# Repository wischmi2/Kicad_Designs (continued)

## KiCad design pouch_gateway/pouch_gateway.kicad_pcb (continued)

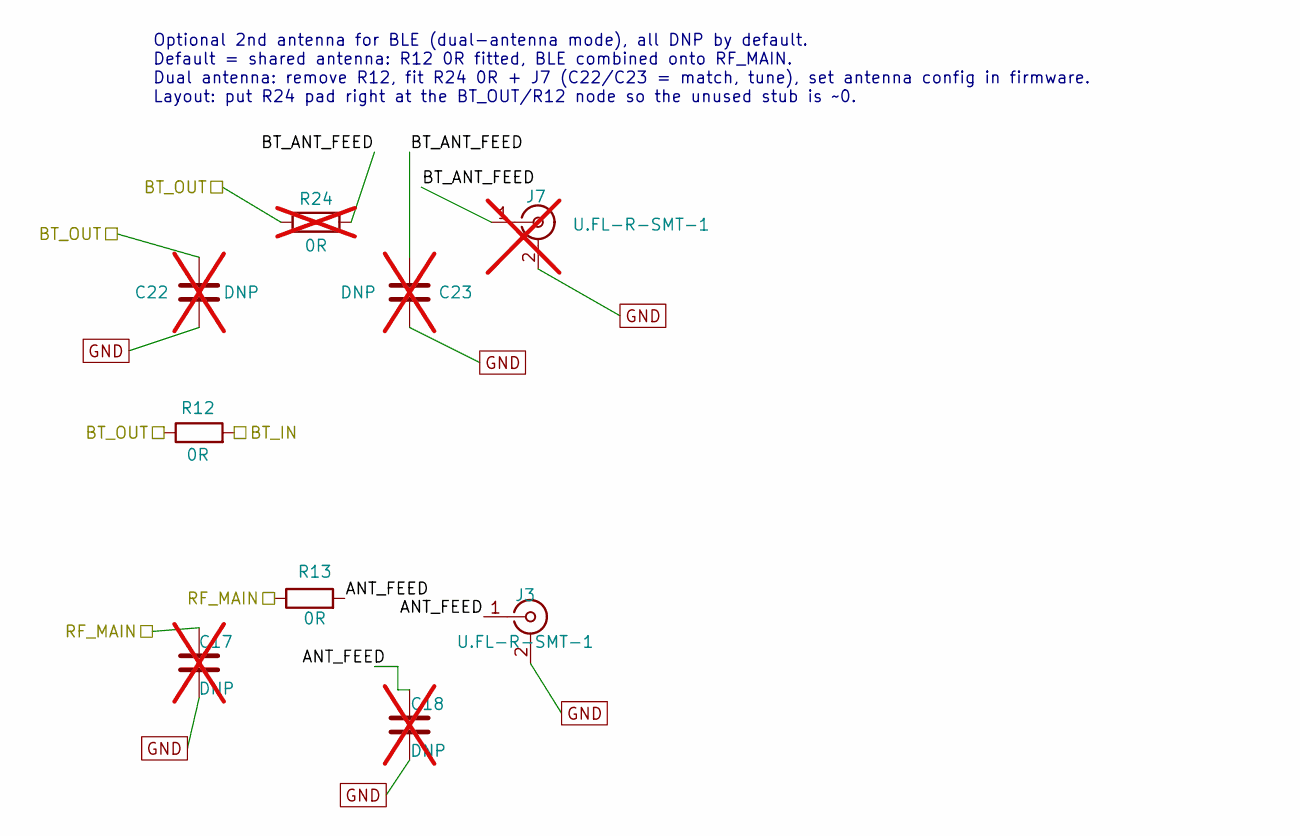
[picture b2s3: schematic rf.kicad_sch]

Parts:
C17, C18: DNP; C_0402_1005Metric; not fitted
C22, C23: DNP; C_0402_1005Metric; LCSC C1525; not fitted
J3: U.FL-R-SMT-1; U.FL_Hirose_U.FL-R-SMT-1_Vertical; LCSC C128668
J7: U.FL-R-SMT-1; U.FL_Hirose_U.FL-R-SMT-1_Vertical; LCSC C128668; not fitted
R12, R13: 0R; R_0402_1005Metric; LCSC C17168
R24: 0R; R_0402_1005Metric; LCSC C17168; not fitted

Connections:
/MCU/BT_IN: R12.2; also elsewhere on the board
/MCU/BT_OUT: C22.1, R12.1, R24.1; also elsewhere on the board
/MCU/RF_MAIN: C17.1, R13.1; also elsewhere on the board
/RF/ANT_FEED: C18.1, J3.1 (In), R13.2
/RF/BT_ANT_FEED: C23.1, J7.1 (In), R24.2
GND: C17.2, C18.2, C22.2, C23.2, J3.2 (Ext), J7.2 (Ext); also elsewhere on the board

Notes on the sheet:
Optional 2nd antenna for BLE (dual-antenna mode), all DNP by default. Default = shared antenna: R12 0R fitted, BLE combined onto RF_MAIN. Dual antenna: remove R12, fit R24 0R + J7 (C22/C23 = match, tune), set antenna config in firmware. Layout: put R24 pad right at the BT_OUT/R12 node so the unused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

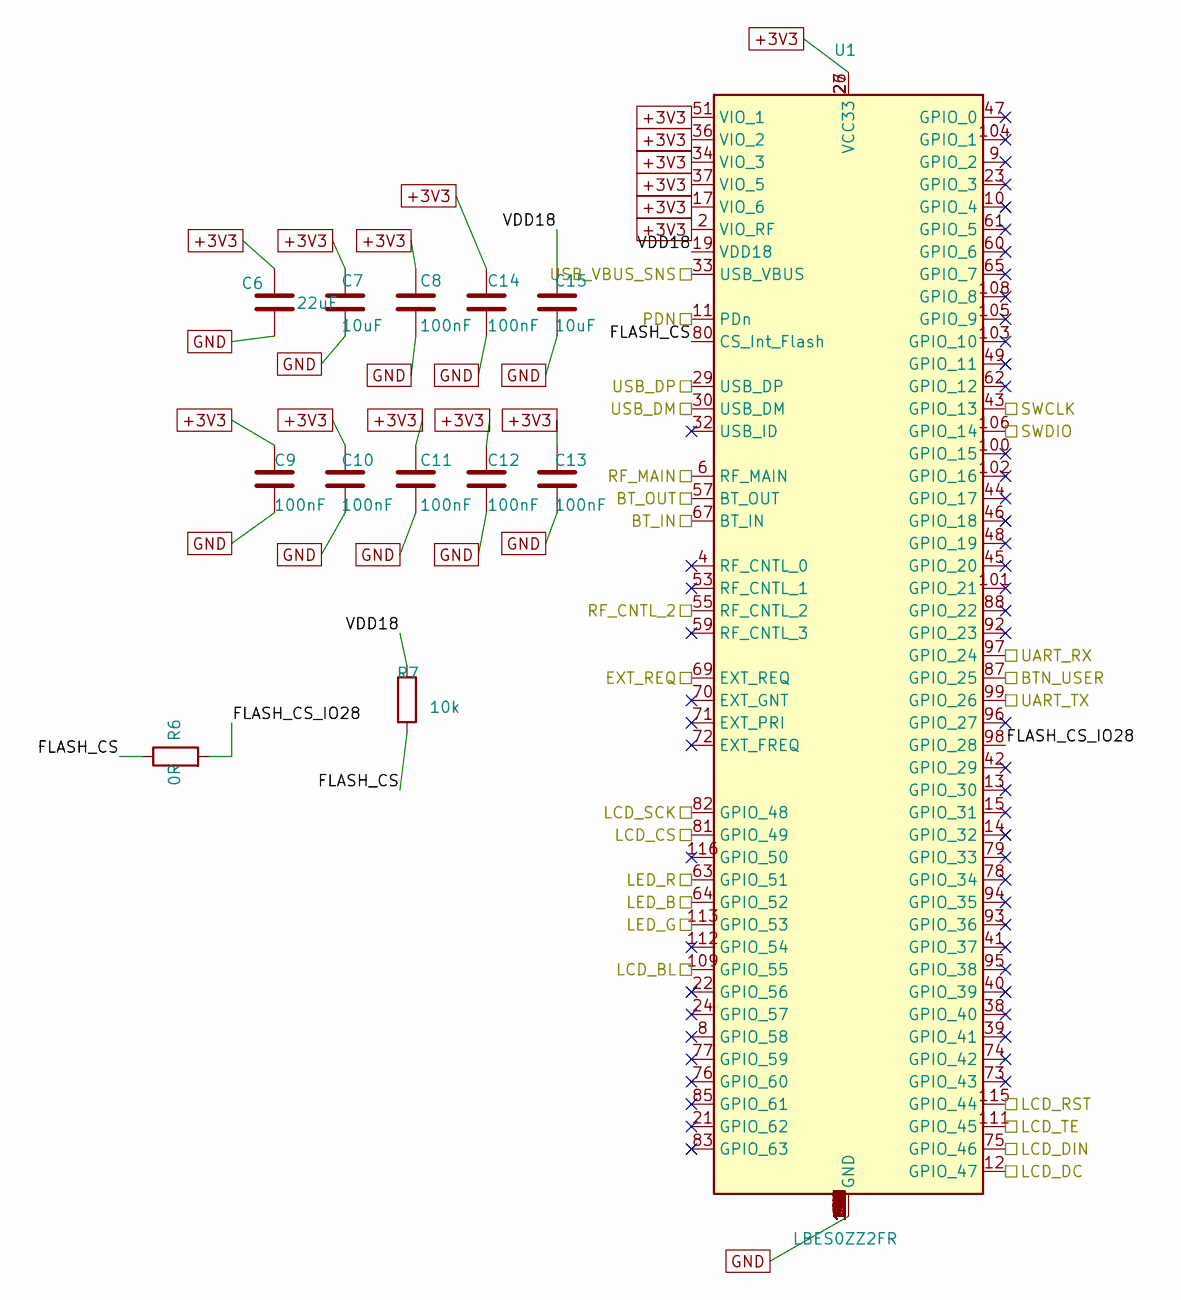
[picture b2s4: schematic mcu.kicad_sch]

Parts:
C6: 22uF; C_0805_2012Metric; LCSC C45783
C7, C15: 10uF; C_0603_1608Metric; LCSC C19702
C8, C9, C10, C11, C12, C13, C14: 100nF; C_0402_1005Metric; LCSC C1525
R6: 0R; R_0402_1005Metric; LCSC C17168
R7: 10k; R_0402_1005Metric; LCSC C25744
U1: LBES0ZZ2FR; Murata_LBES0ZZ2FR; MPN LBES0ZZ2FR-580

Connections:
+3V3: C6.1, C7.1, C8.1, C9.1, C10.1, C11.1, C12.1, C13.1, C14.1, U1.2 (VIO_RF), U1.17 (VIO_6), U1.26 (VCC33), U1.27 (VCC33), U1.34 (VIO_3), U1.36 (VIO_2), U1.37 (VIO_5), U1.51 (VIO_1); also elsewhere on the board
/MCU/BTN_USER: U1.87 (GPIO_25); also elsewhere on the board
/MCU/BT_IN: U1.67 (BT_IN); also elsewhere on the board
/MCU/BT_OUT: U1.57 (BT_OUT); also elsewhere on the board
/MCU/EXT_REQ: U1.69 (EXT_REQ); also elsewhere on the board
/MCU/FLASH_CS: R6.1, R7.2, U1.80 (CS_Int_Flash)
/MCU/FLASH_CS_IO28: R6.2, U1.98 (GPIO_28)
/MCU/LCD_BL: U1.109 (GPIO_55); also elsewhere on the board
/MCU/LCD_CS: U1.81 (GPIO_49); also elsewhere on the board
/MCU/LCD_DC: U1.12 (GPIO_47); also elsewhere on the board
/MCU/LCD_DIN: U1.75 (GPIO_46); also elsewhere on the board
/MCU/LCD_RST: U1.115 (GPIO_44); also elsewhere on the board
/MCU/LCD_SCK: U1.82 (GPIO_48); also elsewhere on the board
/MCU/LCD_TE: U1.111 (GPIO_45); also elsewhere on the board
/MCU/LED_B: U1.64 (GPIO_52); also elsewhere on the board
/MCU/LED_G: U1.113 (GPIO_53); also elsewhere on the board
/MCU/LED_R: U1.63 (GPIO_51); also elsewhere on the board
/MCU/PDN: U1.11 (PDn); also elsewhere on the board
/MCU/RF_CNTL_2: U1.55 (RF_CNTL_2); also elsewhere on the board
/MCU/RF_MAIN: U1.6 (RF_MAIN); also elsewhere on the board
/MCU/SWCLK: U1.43 (GPIO_13); also elsewhere on the board
/MCU/SWDIO: U1.106 (GPIO_14); also elsewhere on the board
/MCU/UART_RX: U1.97 (GPIO_24); also elsewhere on the board
/MCU/UART_TX: U1.99 (GPIO_26); also elsewhere on the board
/MCU/USB_DM: U1.30 (USB_DM); also elsewhere on the board
/MCU/USB_DP: U1.29 (USB_DP); also elsewhere on the board
/MCU/USB_VBUS_SNS: U1.33 (USB_VBUS); also elsewhere on the board
/MCU/VDD18: C15.1, R7.1, U1.19 (VDD18)
GND: C6.2, C7.2, C8.2, C9.2, C10.2, C11.2, C12.2, C13.2, C14.2, C15.2, U1.1 (GND), U1.3 (GND), U1.5 (GND), U1.7 (GND), U1.16 (GND), U1.18 (GND), U1.20 (GND), U1.25 (GND), U1.28 (GND), U1.31 (GND), U1.35 (GND), U1.50 (GND), U1.52 (GND), U1.54 (GND), U1.56 (GND), U1.58 (GND), U1.66 (GND), U1.68 (GND), U1.84 (GND), U1.86 (GND), U1.89 (GND), U1.90 (GND), U1.91 (GND), U1.107 (GND), U1.110 (GND), U1.114 (GND), U1.117 (GND), U1.118 (GND), U1.119 (GND), U1.120 (GND), U1.121 (GND), U1.122 (GND), U1.123 (GND), U1.124 (GND), U1.125 (GND), U1.126 (GND), U1.127 (GND), U1.128 (GND), U1.129 (GND), U1.130 (GND), U1.131 (GND), U1.132 (GND), U1.133 (GND), U1.134 (GND), U1.135 (GND), U1.136 (GND), U1.137 (GND), U1.138 (GND), U1.139 (GND), U1.140 (GND); also elsewhere on the board

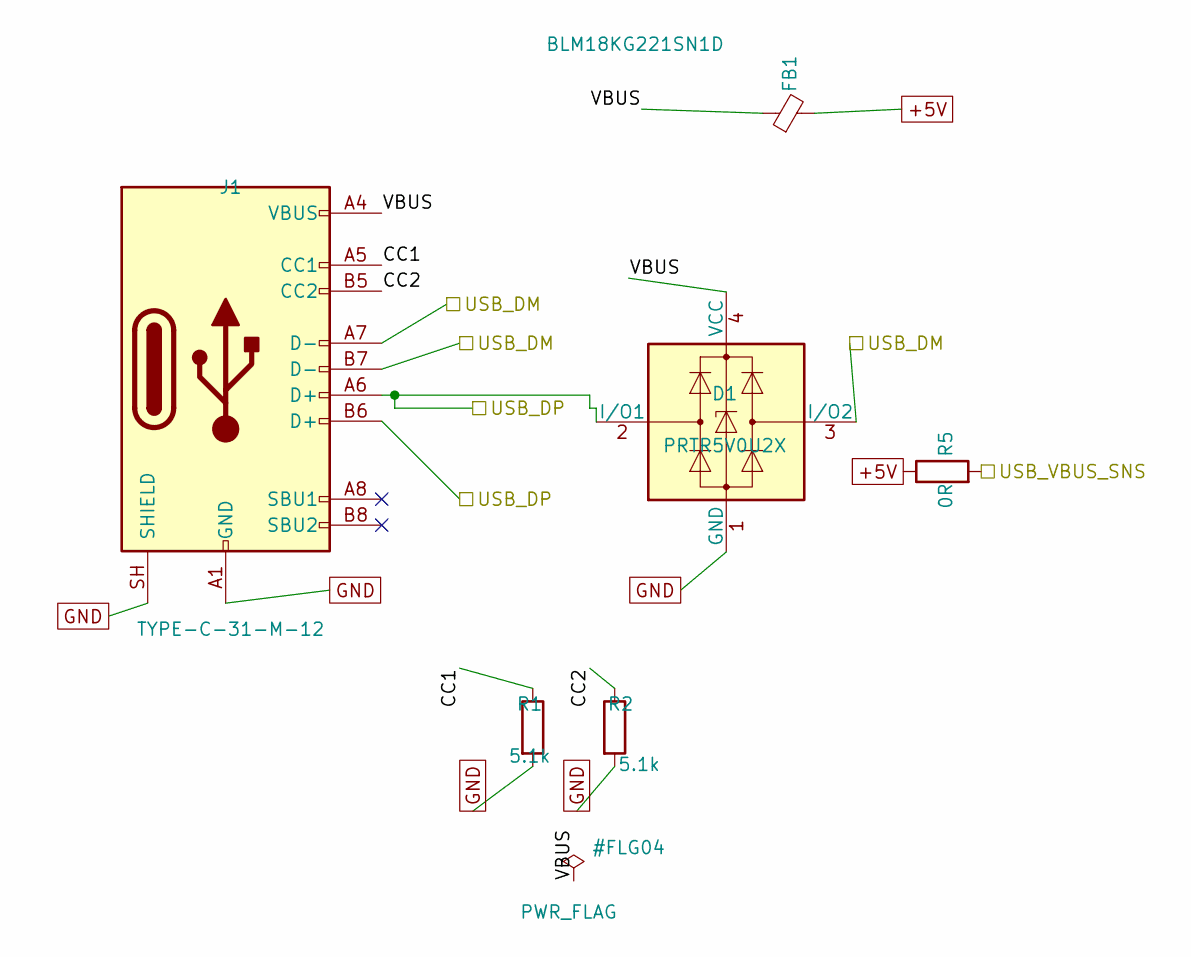
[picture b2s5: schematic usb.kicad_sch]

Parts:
D1: PRTR5V0U2X; SOT-143; LCSC C21713980
FB1: BLM18KG221SN1D; L_0603_1608Metric; LCSC C88980
J1: TYPE-C-31-M-12; USB_C_Receptacle_HRO_TYPE-C-31-M-12; LCSC C165948
R1, R2: 5.1k; R_0402_1005Metric; LCSC C25905
R5: 0R; R_0402_1005Metric; LCSC C17168

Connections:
+5V: FB1.2, R5.1; also elsewhere on the board
/MCU/USB_DM: D1.3 (I/O2), J1.A7 (D-), J1.B7 (D-); also elsewhere on the board
/MCU/USB_DP: D1.2 (I/O1), J1.A6 (D+), J1.B6 (D+); also elsewhere on the board
/MCU/USB_VBUS_SNS: R5.2; also elsewhere on the board
/USB/CC1: J1.A5 (CC1), R1.1
/USB/CC2: J1.B5 (CC2), R2.1
/USB/VBUS: D1.4 (VCC), FB1.1, J1.A4 (VBUS), J1.A9 (VBUS), J1.B4 (VBUS), J1.B9 (VBUS)
GND: D1.1 (GND), J1.A1 (GND), J1.A12 (GND), J1.B1 (GND), J1.B12 (GND), J1.SH (SHIELD), R1.2, R2.2; also elsewhere on the board

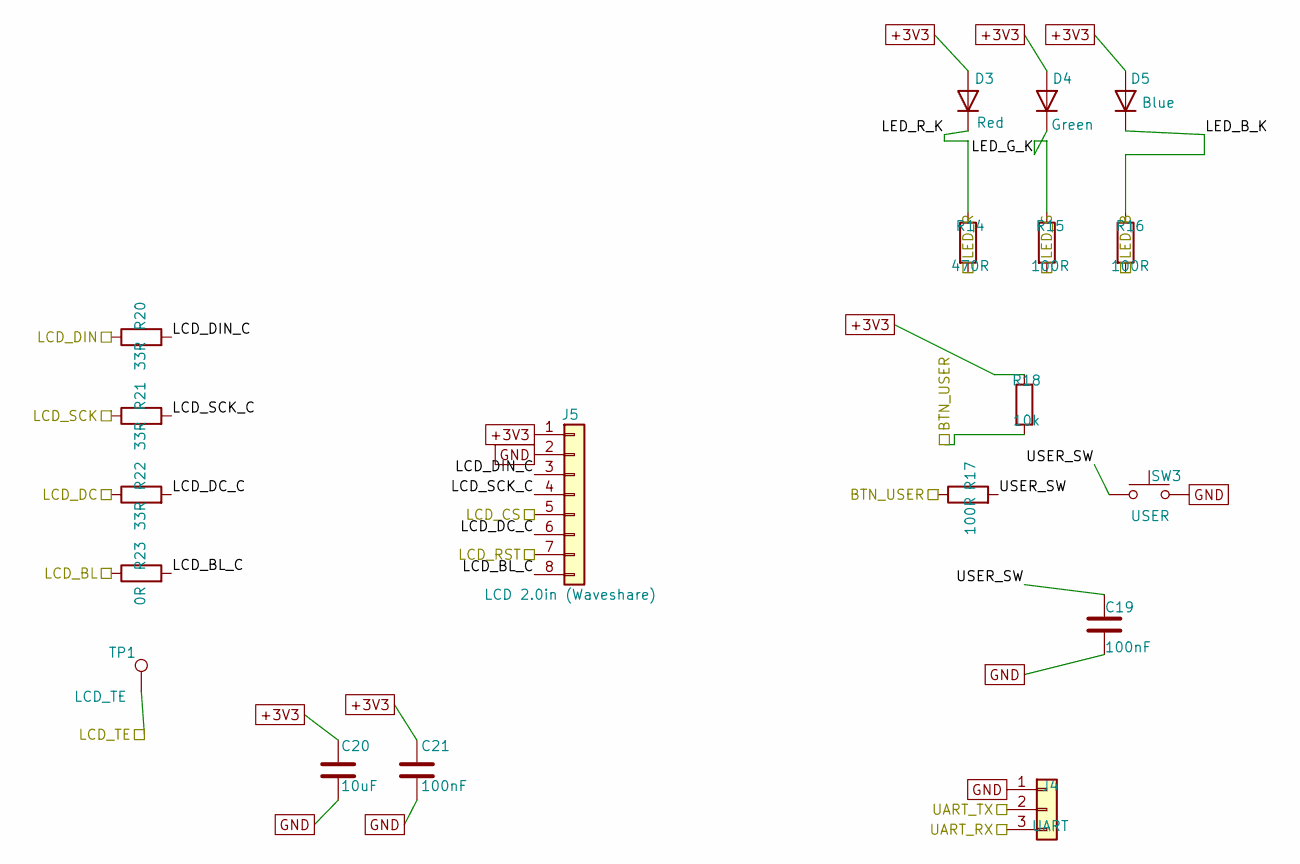
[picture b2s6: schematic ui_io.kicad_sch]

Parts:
C19, C21: 100nF; C_0402_1005Metric; LCSC C1525
C20: 10uF; C_0603_1608Metric; LCSC C19702
D3: Red; LED_0603_1608Metric; LCSC C2286
D4: Green; LED_0805_2012Metric; LCSC C2297
D5: Blue; LED_0603_1608Metric; LCSC C125096
J4: UART; PinHeader_1x03_P2.54mm_Vertical; MPN PZ254V-11-03P; LCSC C2937625
J5: LCD 2.0in (Waveshare); JST_PH_S8B-PH-K_1x08_P2.00mm_Horizontal; MPN S8B-PH-K-S(LF)(SN); LCSC C157915
R14: 470R; R_0402_1005Metric; LCSC C25117
R15, R16, R17: 100R; R_0402_1005Metric; LCSC C25076
R18: 10k; R_0402_1005Metric; LCSC C25744
R20, R21, R22: 33R; R_0402_1005Metric; LCSC C25105
R23: 0R; R_0402_1005Metric; LCSC C17168
SW3: USER; SW_Push_1P1T_NO_CK_KMR2; LCSC C72443
TP1: LCD_TE; TestPoint_Pad_D1.0mm

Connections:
+3V3: C20.1, C21.1, D3.2 (A), D4.2 (A), D5.2 (A), J5.1, R18.1; also elsewhere on the board
/MCU/BTN_USER: R17.1, R18.2; also elsewhere on the board
/MCU/LCD_BL: R23.1; also elsewhere on the board
/MCU/LCD_CS: J5.5; also elsewhere on the board
/MCU/LCD_DC: R22.1; also elsewhere on the board
/MCU/LCD_DIN: R20.1; also elsewhere on the board
/MCU/LCD_RST: J5.7; also elsewhere on the board
/MCU/LCD_SCK: R21.1; also elsewhere on the board
/MCU/LCD_TE: TP1.1 (1_1); also elsewhere on the board
/MCU/LED_B: R16.2; also elsewhere on the board
/MCU/LED_G: R15.2; also elsewhere on the board
/MCU/LED_R: R14.2; also elsewhere on the board
/MCU/UART_RX: J4.3; also elsewhere on the board
/MCU/UART_TX: J4.2; also elsewhere on the board
/UI_IO/LCD_BL_C: J5.8, R23.2
/UI_IO/LCD_DC_C: J5.6, R22.2
/UI_IO/LCD_DIN_C: J5.3, R20.2
/UI_IO/LCD_SCK_C: J5.4, R21.2
/UI_IO/LED_B_K: D5.1 (K), R16.1
/UI_IO/LED_G_K: D4.1 (K), R15.1
/UI_IO/LED_R_K: D3.1 (K), R14.1
/UI_IO/USER_SW: C19.1, R17.2, SW3.1; also elsewhere on the board
GND: C19.2, C20.2, C21.2, J4.1, J5.2, SW3.2; also elsewhere on the board

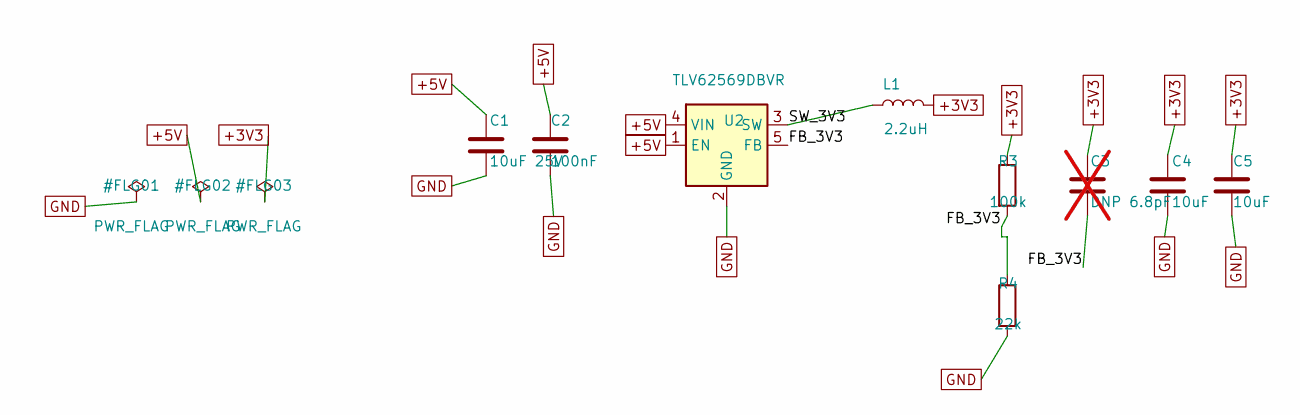
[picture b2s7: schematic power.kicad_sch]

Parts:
C1: 10uF 25V; C_0603_1608Metric; LCSC C96446
C2: 100nF; C_0402_1005Metric; LCSC C1525
C3: DNP 6.8pF; C_0402_1005Metric; not fitted
C4, C5: 10uF; C_0603_1608Metric; LCSC C19702
L1: 2.2uH; L_Sunlord_SWPA4020S; MPN SWPA4020S2R2MT; LCSC C83423
R3: 100k; R_0402_1005Metric; LCSC C25741
R4: 22k; R_0402_1005Metric; LCSC C25768
U2: TLV62569DBVR; SOT-23-5; LCSC C141836

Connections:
+3V3: C3.1, C4.1, C5.1, L1.2, R3.1; also elsewhere on the board
+5V: C1.1, C2.1, U2.1 (EN), U2.4 (VIN); also elsewhere on the board
/Power/FB_3V3: C3.2, R3.2, R4.1, U2.5 (FB)
/Power/SW_3V3: L1.1, U2.3 (SW)
GND: C1.2, C2.2, C4.2, C5.2, R4.2, U2.2 (GND); also elsewhere on the board

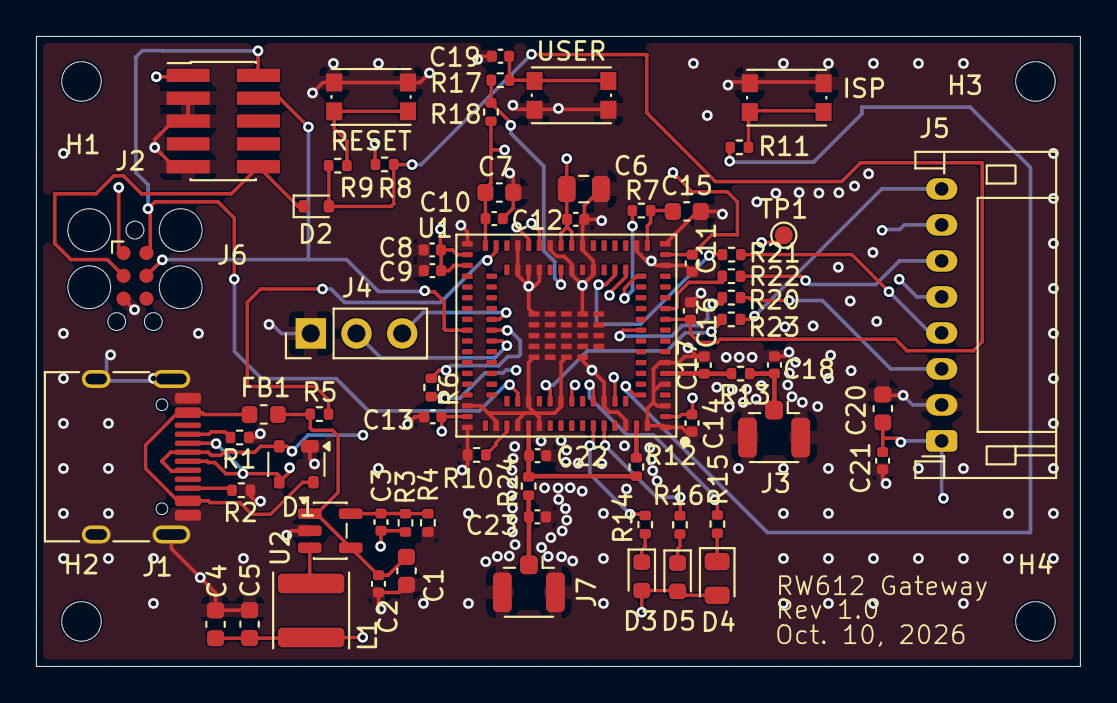
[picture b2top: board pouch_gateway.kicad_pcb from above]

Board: 4 copper layers, 58.0 x 35.0 mm, 70 parts (0 on the bottom side), 48 nets.

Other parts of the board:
ISP: ISP; SW_Push_1P1T_NO_CK_KMR2
RESET: RESET; SW_Push_1P1T_NO_CK_KMR2
USER: USER; SW_Push_1P1T_NO_CK_KMR2

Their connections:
/Reset_Debug_Boot/ISP_SW: ISP.1; also elsewhere on the board
/Reset_Debug_Boot/RST_SW: RESET.1; also elsewhere on the board
/UI_IO/USER_SW: USER.1; also elsewhere on the board
GND: ISP.2, RESET.2, USER.2; also elsewhere on the board

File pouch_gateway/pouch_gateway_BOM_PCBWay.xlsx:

|  |  | pouch_gateway — PCB Assembly BOM
Item # | *Designator | *Qty | Manufacturer | *Mfg Part # | Description / Value | *Package/Footprint | Type | Your Instructions / Notes
1 | C2,C8,C9,C10,C11,C12,C13,C14,C16,C19,C21 | 11 | Samsung Electro-Mechanics | CL05B104KO5NNNC | CAP CER 100nF 16V X7R ±10% 0402 | 0402 | SMD | LCSC: C1525
2 | C1 | 1 | Samsung Electro-Mechanics | CL10A106MA8NRNC | CAP CER 10uF 25V X5R ±20% 0603 | 0603 | SMD | LCSC: C96446 (25V rating required)
3 | C4,C5,C7,C15,C20 | 5 | Samsung Electro-Mechanics | CL10A106KP8NNNC | CAP CER 10uF 10V X5R ±10% 0603 | 0603 | SMD | LCSC: C19702
4 | C6 | 1 | Samsung Electro-Mechanics | CL21A226MAQNNNE | CAP CER 22uF 25V X5R ±20% 0805 | 0805 | SMD | LCSC: C45783
5 | R5,R6,R12,R13,R23 | 5 | UNI-ROYAL | 0402WGF0000TCE | RES 0 OHM JUMPER 1/16W 0402 | 0402 | SMD | LCSC: C17168
6 | R1,R2,R10,R11 | 4 | UNI-ROYAL | 0402WGF5101TCE | RES 5.1K OHM 1% 1/16W 0402 | 0402 | SMD | LCSC: C25905
7 | R7,R8,R18 | 3 | UNI-ROYAL | 0402WGF1002TCE | RES 10K OHM 1% 1/16W 0402 | 0402 | SMD | LCSC: C25744
8 | R3 | 1 | UNI-ROYAL | 0402WGF1003TCE | RES 100K OHM 1% 1/16W 0402 | 0402 | SMD | LCSC: C25741
9 | R4 | 1 | UNI-ROYAL | 0402WGF2202TCE | RES 22K OHM 1% 1/16W 0402 | 0402 | SMD | LCSC: C25768
10 | R9,R15,R16,R17 | 4 | UNI-ROYAL | 0402WGF1000TCE | RES 100 OHM 1% 1/16W 0402 | 0402 | SMD | LCSC: C25076
11 | R14 | 1 | UNI-ROYAL | 0402WGF4700TCE | RES 470 OHM 1% 1/16W 0402 | 0402 | SMD | LCSC: C25117
12 | R20,R21,R22 | 3 | UNI-ROYAL | 0402WGF330JTCE | RES 33 OHM 1% 1/16W 0402 | 0402 | SMD | LCSC: C25105
13 | FB1 | 1 | Murata | BLM18KG221SN1D | FERRITE BEAD 220 OHM @100MHz 2.2A 0603 | 0603 | SMD | LCSC: C88980
14 | L1 | 1 | Sunlord | SWPA4020S2R2MT | INDUCTOR PWR 2.2uH ±20% 4x4mm SMD | SMD 4.0x4.0mm | SMD | LCSC: C83423
15 | D1 | 1 | GOODWORK | PRTR5V0U2X | TVS ESD 2-CH USB PROTECTION SOT-143 | SOT-143 | SMD | LCSC: C21713980; Nexperia PRTR5V0U2X acceptable alternate. Polarity per silkscr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
16 | D2 | 1 | onsemi | RB521S30T1G | DIODE SCHOTTKY 30V 200mA SOD-523 | SOD-523 | SMD | LCSC: C145179; polarity per silkscreen
17 | D3 | 1 | Hubei KENTO | KT-0603R | LED RED 0603 | 0603 | SMD | LCSC: C2286; polarity per silkscreen
18 | D4 | 1 | Hubei KENTO | KT-0805G | LED GREEN 0805 | 0805 | SMD | LCSC: C2297; polarity per silkscreen
19 | D5 | 1 | Lite-On | LTST-C190TBKT | LED BLUE 0603 | 0603 | SMD | LCSC: C125096; polarity per silkscreen
20 | U1 | 1 | Murata | LBES0ZZ2FR-580 | MODULE WI-FI/BLE (Murata Type 2FR) | Murata LBES0ZZ2FR module, SMD | SMD | No LCSC part #; please quote sourcing. Pin 1 per silkscreen
21 | U2 | 1 | Texas Instruments | TLV62569DBVR | IC REG BUCK ADJ 2A SOT-23-5 | SOT-23-5 | SMD | LCSC: C141836; pin 1 per silkscreen
22 | J1 | 1 | Korean Hroparts Elec (HRO) | TYPE-C-31-M-12 | CONN USB TYPE-C RCPT 16P SMD R/A | SMD | SMD | LCSC: C165948
23 | J2 | 1 | Samtec | FTSH-105-01-L-DV-K-TR | CONN HDR 2x5 1.27mm SMD VERT (SWD) | 2x5 P1.27mm SMD | SMD | LCSC: C448647; pin 1 per silkscreen
24 | J3 | 1 | Hirose | U.FL-R-SMT-1(60) | CONN U.FL RF COAX RCPT SMD | SMD | SMD | LCSC: C128668
25 | ISP,RESET,USER | 3 | C&K | KMR221GLFS | SWITCH TACTILE SPST-NO 50mA 32V SMD | SMD 4.6x2.8mm | SMD | LCSC: C72443
26 | J4 | 1 | XFCN | PZ254V-11-03P | CONN HDR 1x3 2.54mm VERT THT | 1x3 P2.54mm THT | thru-hole | LCSC: C2937625
27 | J5 | 1 | JST | S8B-PH-K-S(LF)(SN) | CONN HDR PH 8POS 2.0mm R/A THT | 1x8 P2.00mm R/A THT | thru-hole | LCSC: C157915
28 | C3 | 1 |  |  | CAP CER 6.8pF 0402 (not fitted) | 0402 | DNS | Do not populate
29 | C17,C18 | 2 |  |  | CAP CER 0402 (not fitted) | 0402 | DNS | Do not populate
30 | C22,C23 | 2 |  |  | CAP CER 100nF 0402 (not fitted) | 0402 | DNS | Do not populate
31 | R24 | 1 |  |  | RES 0 OHM 0402 (not fitted) | 0402 | DNS | Do not populate
32 | J7 | 1 |  |  | CONN U.FL RF COAX RCPT SMD (not fitted) | SMD | DNS | Do not populate
Need a quick and accurante quote? Need an efficient production? Please read SMT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
Click for Instructions on How to Create a BOM

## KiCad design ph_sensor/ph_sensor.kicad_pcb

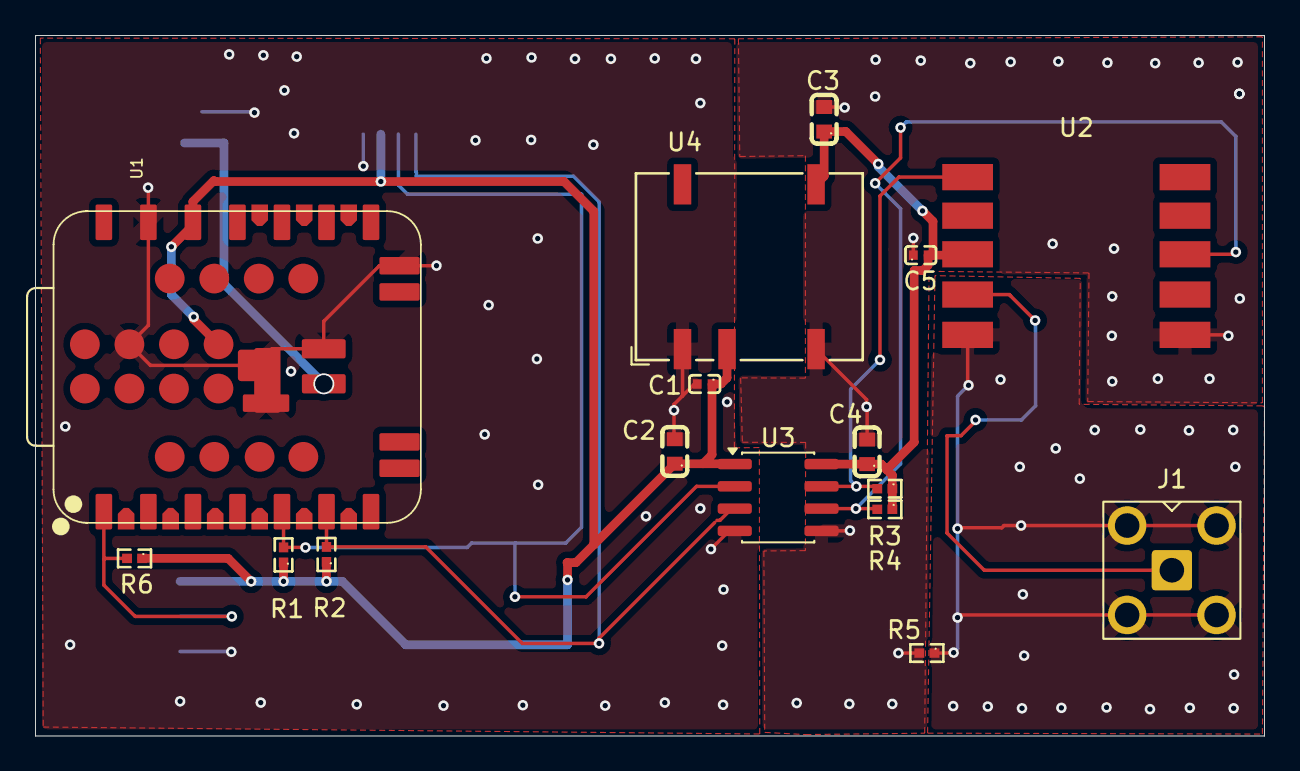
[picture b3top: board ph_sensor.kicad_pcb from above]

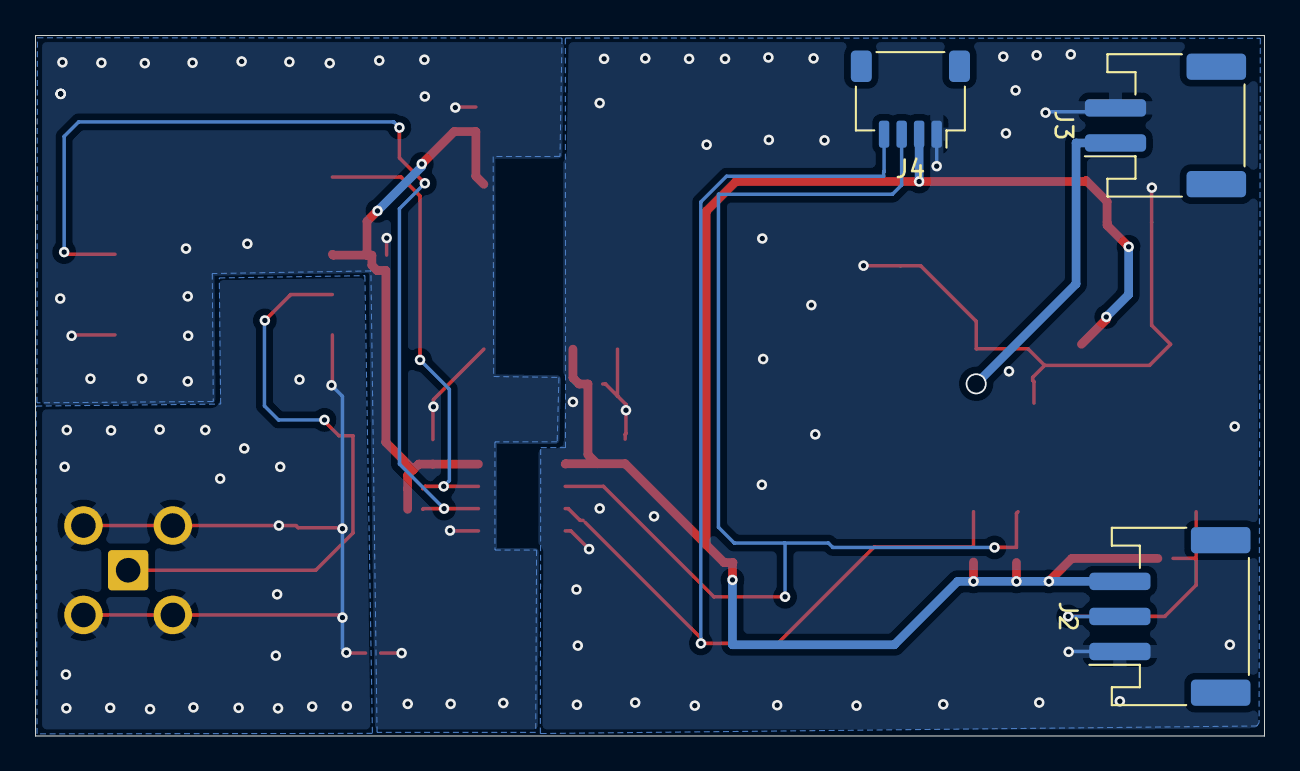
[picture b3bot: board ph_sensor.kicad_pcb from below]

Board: 2 copper layers, 70.1 x 40.0 mm, 19 parts (3 on the bottom side), 12 nets.

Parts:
C1, C5: 1uF; C0402
C2, C4: 100nF; C0603
C3: 2.2uF; C0603
J1: Conn_Coaxial_Small; SMA_BAT_Wireless_BWSMA-KWE-Z001
J2: Conn_01x03; JST_PH_S3B-PH-SM4-TB_1x03-1MP_P2.00mm_Horizontal
J3: Conn_01x02; JST_PH_S2B-PH-SM4-TB_1x02-1MP_P2.00mm_Horizontal
J4: Conn_01x04; JST_SH_SM04B-SRSS-TB_1x04-1MP_P1.00mm_Horizontal
R1, R2, R3, R4, R6: 4.7k; R0402
R5: 0; R0402
U1: XIAO-nRF54LM20A-SMD
U2: Atlas_pH_OEM
U3: ADuM1250; SOIC-8_3.9x4.9mm_P1.27mm
U4: NXE1S0303MC; Converter_DCDC_Murata_NXExSxxxxMC_SMD

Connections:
+3.3V: C1.1, C2.1, J2.3, J4.2, R1.1, R2.1, R6.1, U1.12 (3V3_OUT), U1.39 (3V3_OUT), U3.1 (VDD1), U4.3 (+Vin)
+3v3V_ISO: C3.1, C4.1, C5.2, R3.1, R4.1, U2.3 (VCC), U3.8 (VDD2), U4.8 (+Vout)
AGND_ISO: J1.2 (Ext), R5.1, U2.5 (PRB_GND)
GND: C1.2, C2.2, J2.1, J3.2, J4.1, U1.13 (GND), U1.35 (GND), U1.41 (GND), U1.42 (GND), U1.46 (GND), U3.4 (GND1), U4.1 (-Vin)
GND_ISO: C3.2, C4.2, C5.1, R5.2, U2.6 (GND), U3.5 (GND2), U4.7 (-Vout)
unnamed: J1.1 (In), U2.4 (PRB)
SCL_H: J4.4, R2.2, U1.6 (D5), U3.3 (SCL1)
SCL_ISO: R4.2, U2.8 (SCL), U3.6 (SCL2)
SDA_H: J4.3, R1.2, U1.5 (D4), U3.2 (SDA1)
SDA_ISO: R3.2, U2.1 (SDA), U3.7 (SDA2)
TEMP_DQ: J2.2, R6.2, U1.1 (D0)
VBAT: J3.1, U1.40 (VBAT)

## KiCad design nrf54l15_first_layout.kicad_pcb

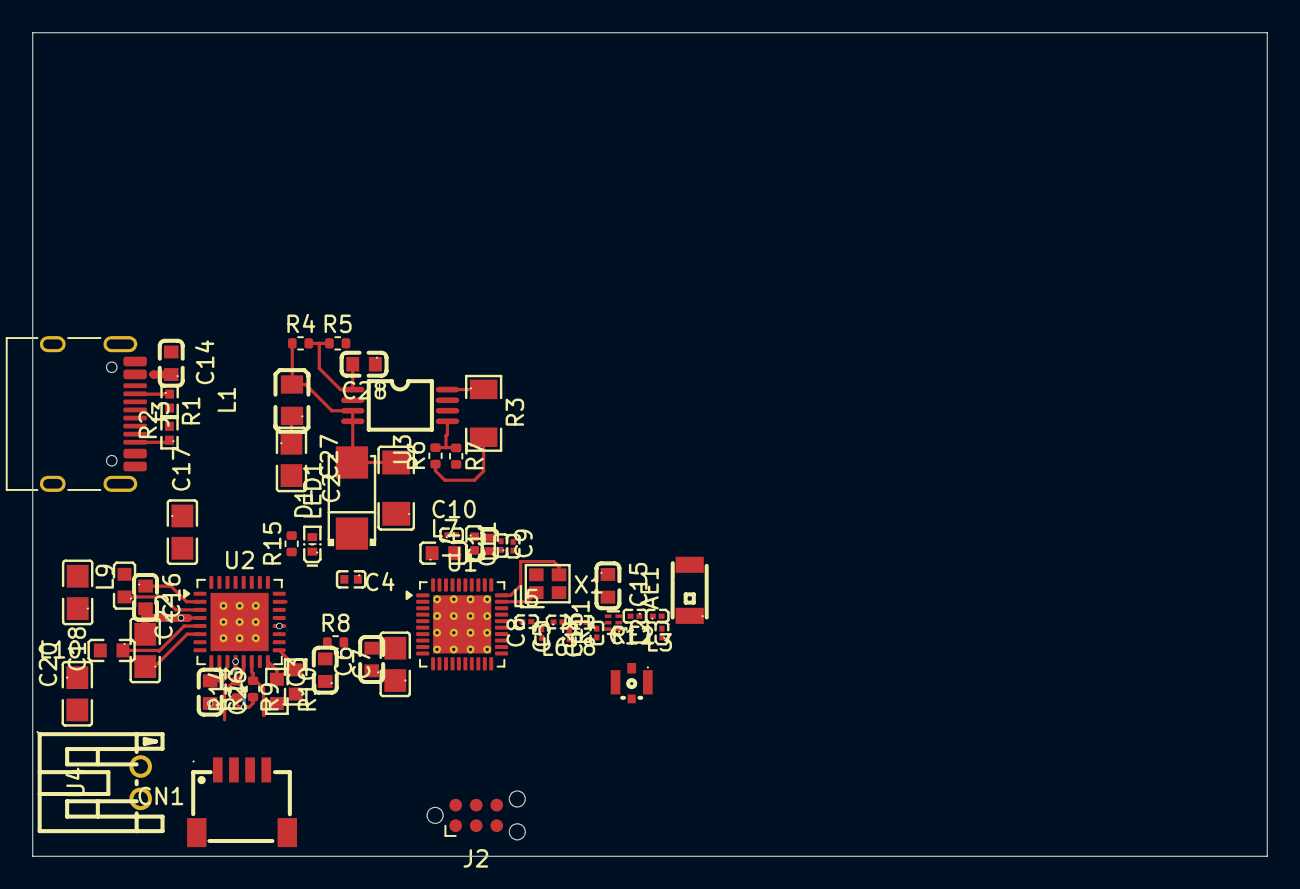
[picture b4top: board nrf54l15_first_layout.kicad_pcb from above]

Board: 4 copper layers, 76.4 x 51.0 mm, 59 parts (0 on the bottom side), 42 nets.

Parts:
AE1: 2450AT18A100E; ANT-SMD_L3.2-W1.6
C1, C10: 2.2uF; C0201
C2: 47uF; C1206
C3: 2.2uF; C0603
C4: 1uF; C0402
C5: 2.0pF; C0201
C6, C14, C15, C26, C28: 100nF; C0603
C7, C17, C18, C20, C22, C27: 10uF; C0805
C8: 1.5pF; C0201
C9: 10nF; C0402
C11: 2.2pF; C0201
C12: 1.0pF; C0201
C13: 0.3pF; C0201
C16: 10uF; C0603
CN1: SM04B-SRSS-TB; CONN-SMD_4P-P1.00_SM04B-SRSS-TB-LF-SN
D1: SS14_C83852; SMA_L4.3-W2.6-LS5.2-RD
J2: TC2030; Tag-Connect_TC2030-IDC-NL_2x03_P1.27mm_Vertical
J3: USB_C_Receptacle_PowerOnly_6P; USB_C_Receptacle_HRO_TYPE-C-31-M-12
L1: SDFL2012S100KTF; L0805
L2, L5: 2.7nH; L0201
L3: 3.9nH; L0201
L4: CBG100505U121T; L0402
L6, L8: 3.5nH; L0201
L7: 4.7uH; L0603
L9, L10: 2.2uH; L0603
LED1: SML-P12MTT86R; LED-SMD_L1.0-W0.6-RD_SML-P12YTT86RR
R1, R2: 5.1k; R0402
R3: 100k; R1206
R4: 3.3M; R_0402_1005Metric
R5, R7: 1M; R_0402_1005Metric
R6: 3.9M; R_0402_1005Metric
R8: 10k; R_0402_1005Metric
R9: 47k; R0603
R10: 150k; R0603
R11: FM8625H; DFN-6_L1.1-W0.7-P0.40-BL
R13, R14: 4.7k; R_0402_1005Metric
R15: 560; R_0402_1005Metric
RF1: ECT818000500; ANT-SMD_ECT818000500
U1: nRF54L15-QDXX; QFN-40-1EP_5x5mm_P0.4mm_EP3.6x3.6mm_ThermalVias
U2: nPM1300-QEXX; QFN-32-1EP_5x5mm_P0.5mm_EP3.6x3.6mm_ThermalVias
U3: SPV1040T; TSSOP-8_L4.4-W3.0-P0.65-LS6.4-BL
U4: S2B-PH-K-S-GW; CONN-TH_S2B-PH-K-S-GW
X1: XL7EL89CKI-111YLC-32M; CRYSTAL-SMD_4P-L2.0-W1.6-BL

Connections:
/npm1300/VSYS: C16.2, C20.2 (2_2), C22.2, R15.1, U2.4 (PVDD), U2.20 (VSYS)
ANT: C13.1, L8.2, R11.5 (ANT)
ANT_SEL: R11.6 (VCTL), U1.21 (P0.01)
CC1: J3.A5 (CC1), R1.1, U2.23 (CC1)
CC2: J3.B5 (CC2), R2.1, U2.24 (CC2)
GND: AE1.2, C1.2, C2.1, C3.1, C4.1, C5.1, C6.1, C7.1, C8.1, C9.2, C10.1, C11.2, C13.2, C14.2, C15.1, C18.1, C26.1, C27.2, C28.1, CN1.1, CN1.5, CN1.6, J2.4, J3.A12 (GND), J3.B12 (GND), J3.SH (SHIELD), L2.1, R1.2, R2.2, R5.2, R7.2, R8.2, R9.1, R10.1, R11.2 (GND), RF1.1 (GND), RF1.3 (GND), RF1.4 (GND), U1.27 (VSS_PA), U1.37 (VSS), U1.41 (VSS), U2.33 (AVSS), U3.2 (GND), U3.6 (ICTRL_MINUS), U3.7 (ICTRL_PLUS), U4.2, X1.2 (GND), X1.4 (GND)
I2C_SCL: CN1.4, R13.2, U1.4 (P1.03), U2.14 (SCL)
I2C_SDA: CN1.3, R14.2, U1.24 (P0.04), U2.13 (SDA)
unnamed: AE1.1 (ANT), L3.1
unnamed: C5.2, L6.2, L8.1
unnamed: C8.2, L5.2, L6.1
unnamed: C12.2, L2.2, L3.2
unnamed: LED1.2 (A), R15.2
unnamed: LED1.1 (C), U2.25 (LED0)
unnamed: C12.1, R11.3 (RF1)
unnamed: R11.1 (RF2), RF1.2 (CONT)
unnamed: L5.1, U1.26 (ANT)
unnamed: L7.1, U1.39 (DCC)
unnamed: C1.1, C9.1, C11.1, L4.2, U1.28 (DECRF), U1.36 (DECA)
unnamed: C10.2, L4.1, L7.2, U1.38 (DECD)
unnamed: U1.29 (XC1), X1.1
unnamed: U1.30 (XC2), X1.3
unnamed: R8.1, U2.18 (NTC)
unnamed: L9.1, U2.3 (SW1)
unnamed: L10.1, U2.5 (SW2)
unnamed: R9.2, U2.17 (VSET1)
unnamed: R10.2, U2.16 (VSET2)
unnamed: C28.2, R4.2, R5.1, U3.1 (MPP-SET)
unnamed: R6.2, R7.1, U3.5 (VCTRL)
unnamed: R3.1, U3.8 (XSHUT)
PVSS1: C16.1, U2.2 (PVSS1)
PVSS2: C22.1, U2.6 (PVSS2)
SOLAR_5p5V: C27.1, L1.1
SPV1040T_VOUT: C2.2, D1.2 (A), L1.2, R3.2, R4.1, R6.1, U3.3 (LX), U3.4 (VOUT)
VBAT: C3.2, U2.15 (SHPHLD), U2.19 (VBAT), U4.1
VBUS: C4.2, C14.1, D1.1 (K), J3.A9 (VBUS), J3.B9 (VBUS), U2.21 (VBUS)
VDDIO: C26.2, R13.1, R14.1, U2.12 (VDDIO)
VOUT1: C6.2, C7.2, C15.2, C18.2, J2.1, L9.2, R11.4 (VDD), U1.9 (VDD), U1.19 (VDD), U1.31 (VDD), U1.40 (VDD), U2.1 (VOUT1)
VOUT2: C17.2, CN1.2, L10.2, U2.32 (VOUT2)
nRF54_RESET: J2.5, U1.25 (~RESET)
nRF54_SWDCLK: J2.3, U1.23 (SWDCLK)
nRF54_SWDIO: J2.2, U1.22 (SWDIO)
